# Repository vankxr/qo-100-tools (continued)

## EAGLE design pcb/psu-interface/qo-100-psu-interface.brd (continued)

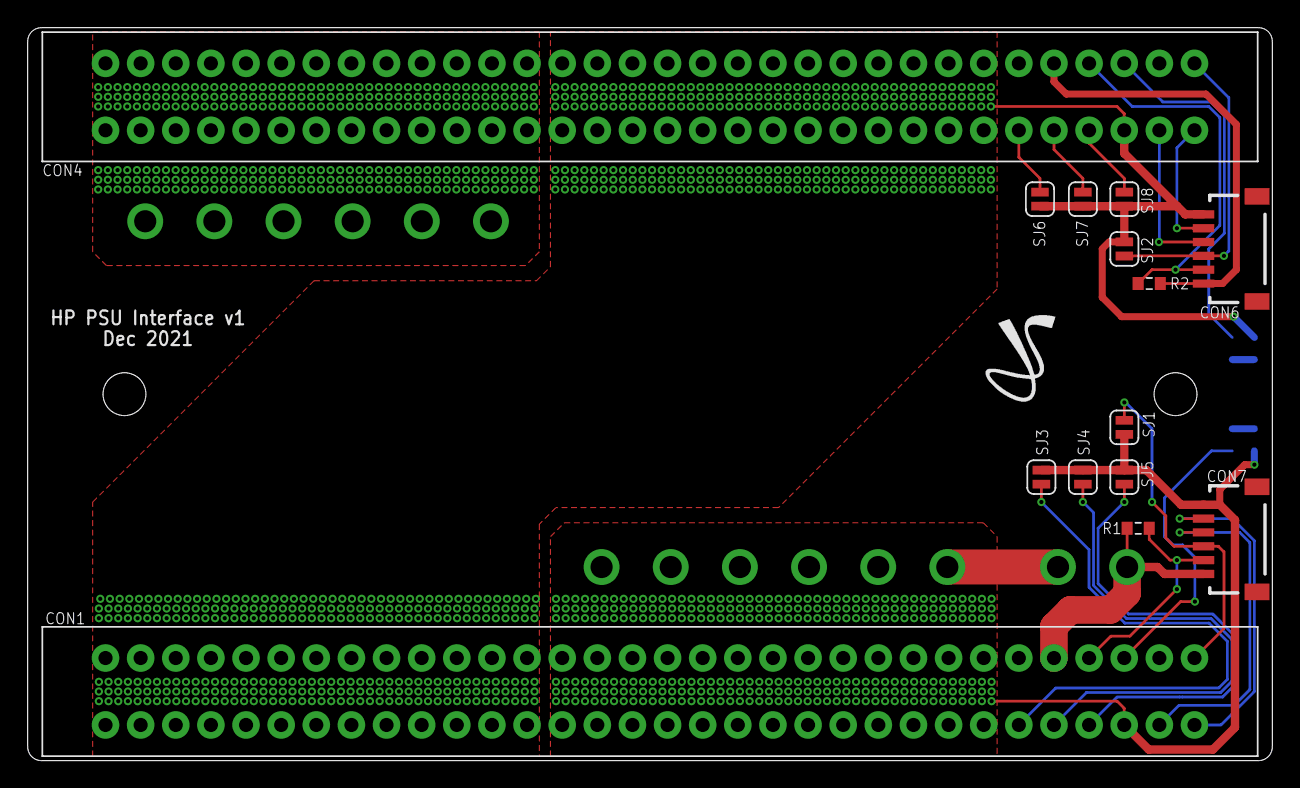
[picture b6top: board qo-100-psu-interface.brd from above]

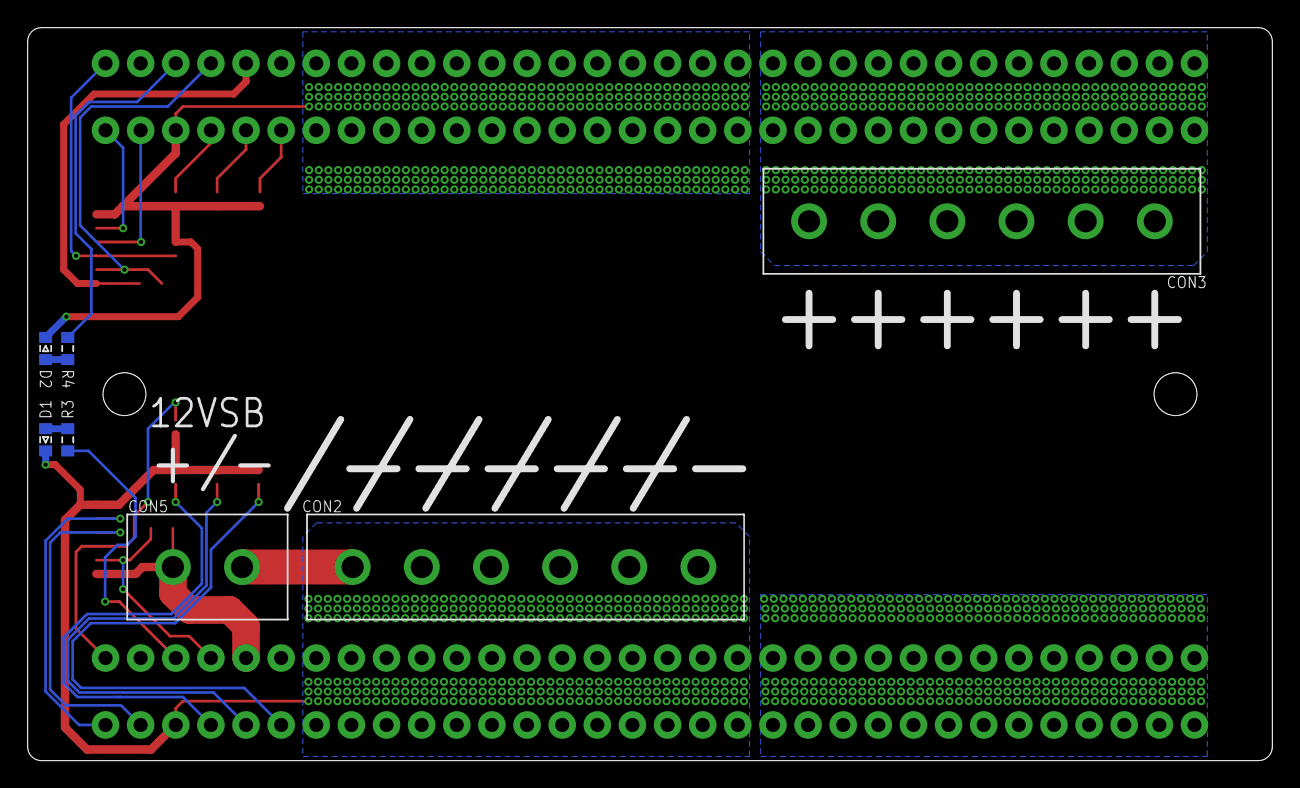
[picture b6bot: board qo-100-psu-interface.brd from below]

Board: 2 copper layers, 90.0 x 53.0 mm, 22 parts (7 on the bottom side), 23 nets.

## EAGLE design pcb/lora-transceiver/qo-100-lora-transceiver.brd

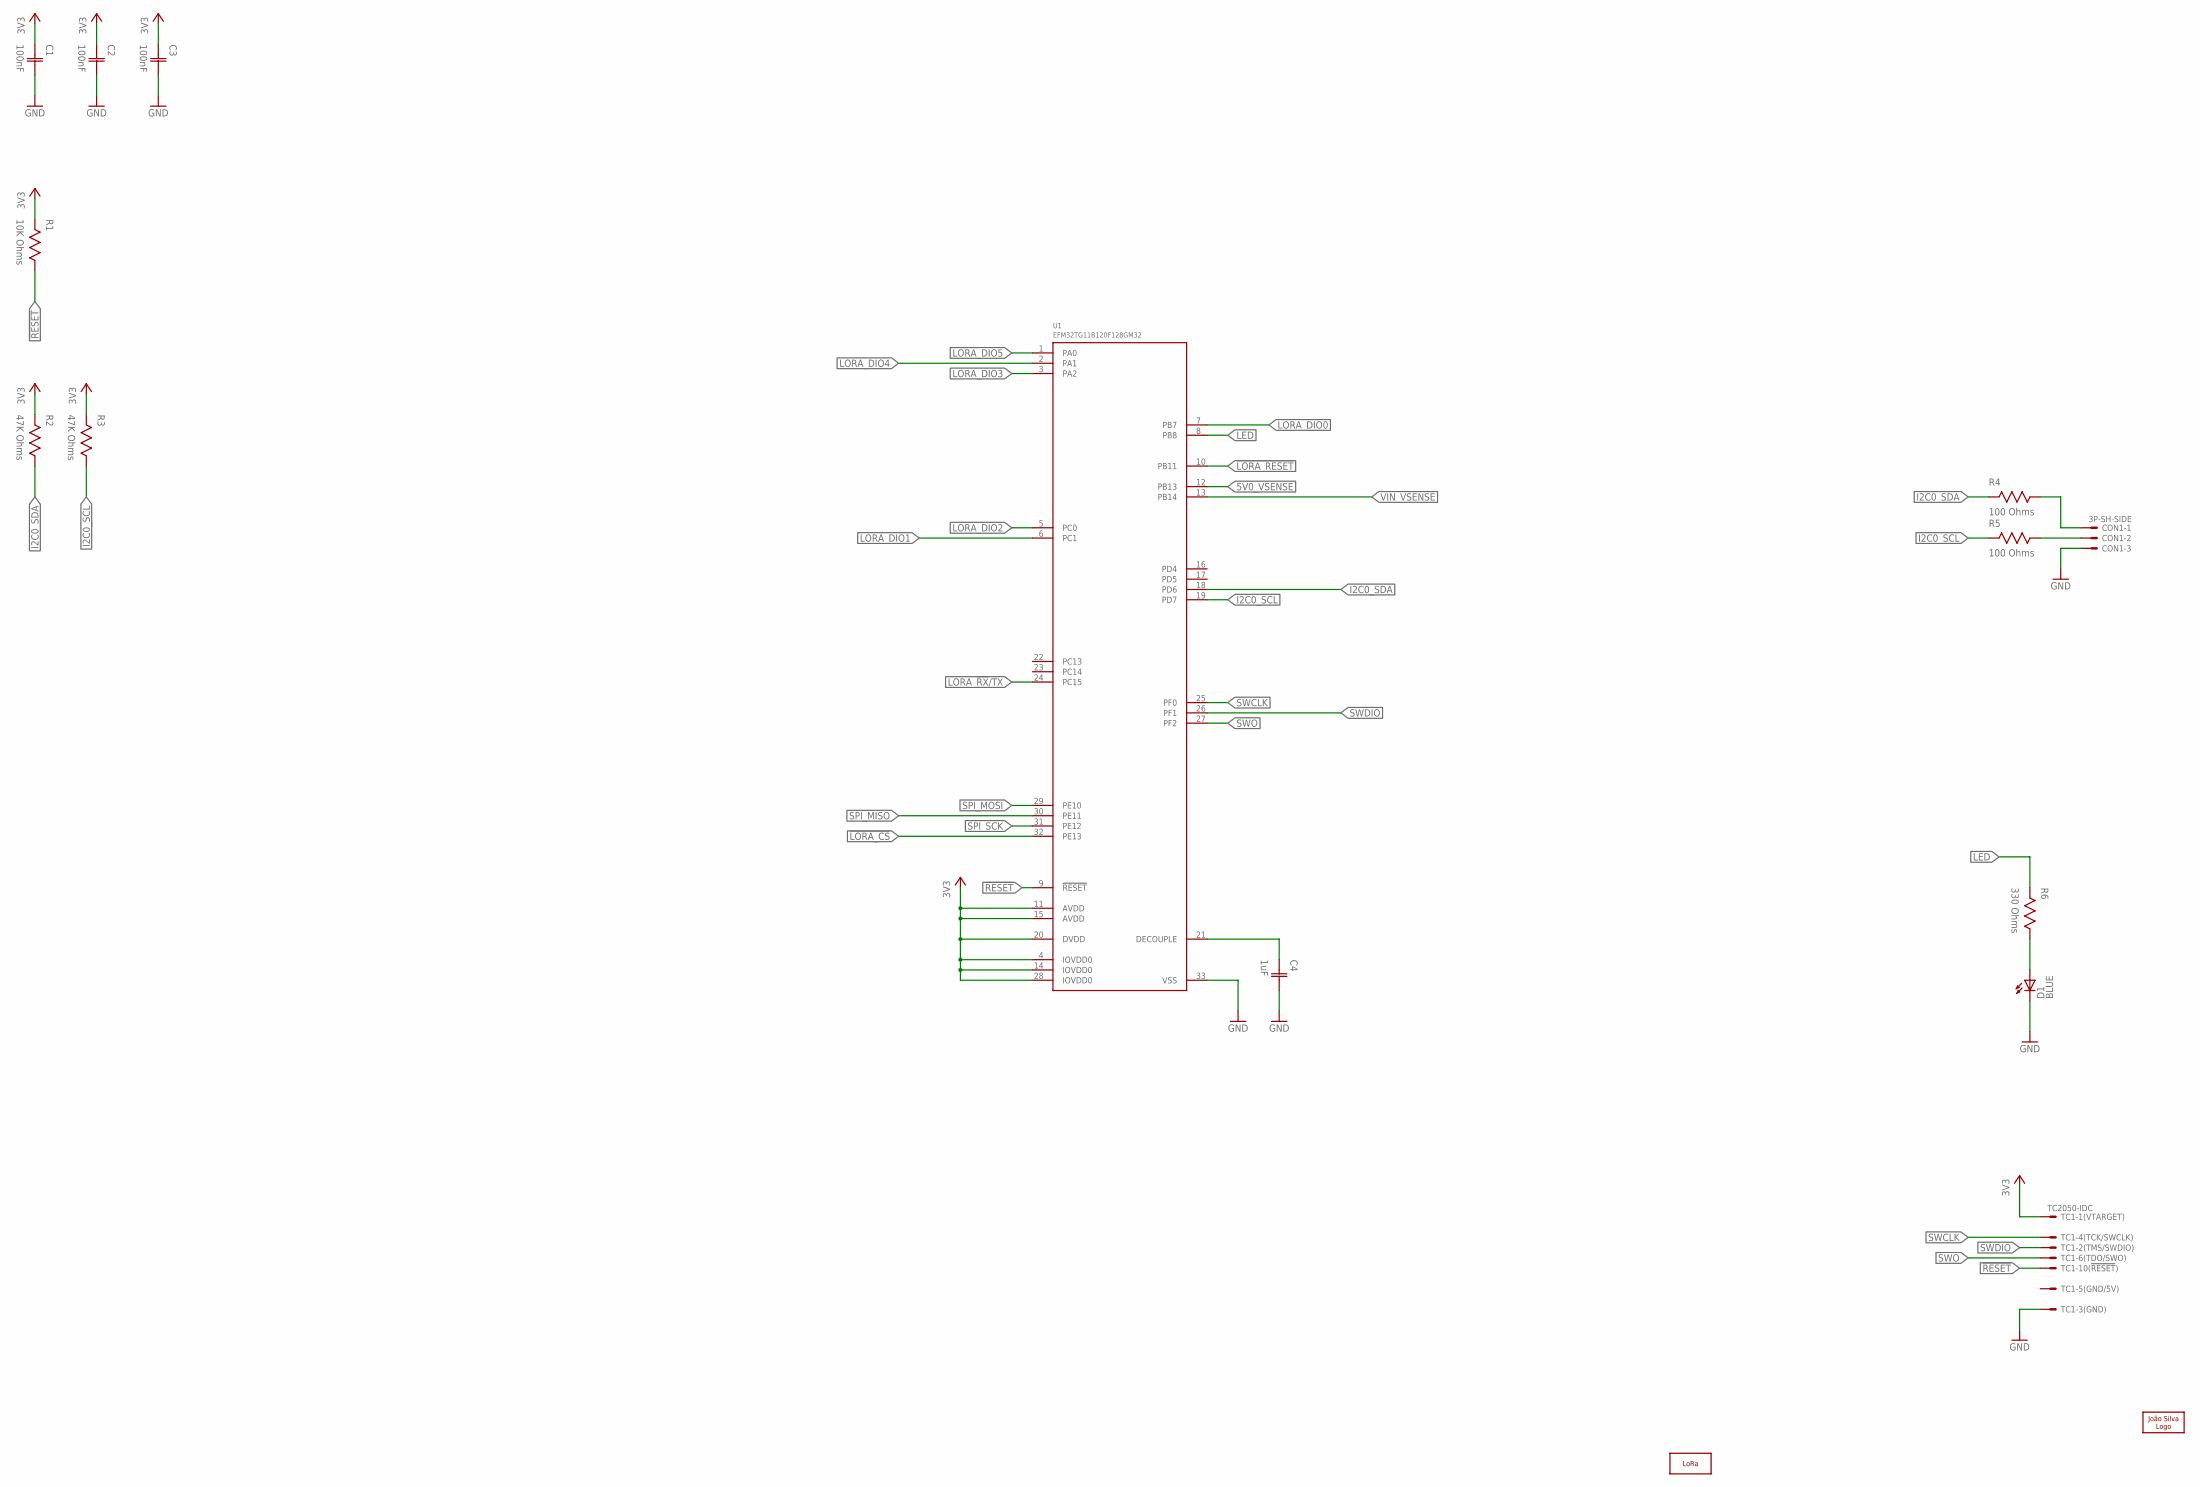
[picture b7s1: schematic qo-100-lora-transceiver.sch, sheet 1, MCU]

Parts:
C1, C2, C3: 100nF; CAP0603
C4: 1uF; CAP0603
CON1: 3P-SH-SIDE; SH-03-SIDE
D1: LED0603; 0603
LOGO1: LORA-10MM; LORA_10MM
LOGO2: JS-10MM; JS_10MM
R1: 10K Ohms; RES0603
R2, R3: 47K Ohms; RES0603
R4, R5: 100 Ohms; RES0603
R6: 330 Ohms; RES0603
TC1: TC2050-IDC
U1: EFM32TG11B120F128GM32; QFN32_0.5P_TG

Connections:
3V3: C1.1 (C1), C2.1 (C1), C3.1 (C1), R1.2, R2.2, R3.2, TC1.1, U1.4 (IOVDD0), U1.11 (AVDD), U1.14 (IOVDD0), U1.15 (AVDD), U1.20 (DVDD), U1.28 (IOVDD0); also elsewhere on the board
5V0_VSENSE: U1.12 (PB13); also elsewhere on the board
!LORA_CS: U1.32 (PE13); also elsewhere on the board
!LORA_RESET: U1.10 (PB11); also elsewhere on the board
!RESET: R1.1, TC1.10, U1.9 (!RESET)
GND: C1.2 (C2), C2.2 (C2), C3.2 (C2), C4.2 (C2), CON1.3, D1.C, TC1.3, U1.33 (VSS); also elsewhere on the board
I2C0_SCL: R3.1, R5.2, U1.19 (PD7)
I2C0_SDA: R2.1, R4.2, U1.18 (PD6)
LED: R6.2, U1.8 (PB8)
LORA_!RX!/TX: U1.24 (PC15); also elsewhere on the board
LORA_DIO0: U1.7 (PB7); also elsewhere on the board
LORA_DIO1: U1.6 (PC1); also elsewhere on the board
LORA_DIO2: U1.5 (PC0); also elsewhere on the board
LORA_DIO3: U1.3 (PA2); also elsewhere on the board
LORA_DIO4: U1.2 (PA1); also elsewhere on the board
LORA_DIO5: U1.1 (PA0); also elsewhere on the board
unnamed: CON1.2, R5.1
unnamed: C4.1 (C1), U1.21 (DECOUPLE)
unnamed: D1.A, R6.1
unnamed: CON1.1, R4.1
SPI_MISO: U1.30 (PE11); also elsewhere on the board
SPI_MOSI: U1.29 (PE10); also elsewhere on the board
SPI_SCK: U1.31 (PE12); also elsewhere on the board
SWCLK: TC1.4, U1.25 (PF0)
SWDIO: TC1.2, U1.26 (PF1)
SWO: TC1.6, U1.27 (PF2)
VIN_VSENSE: U1.13 (PB14); also elsewhere on the board

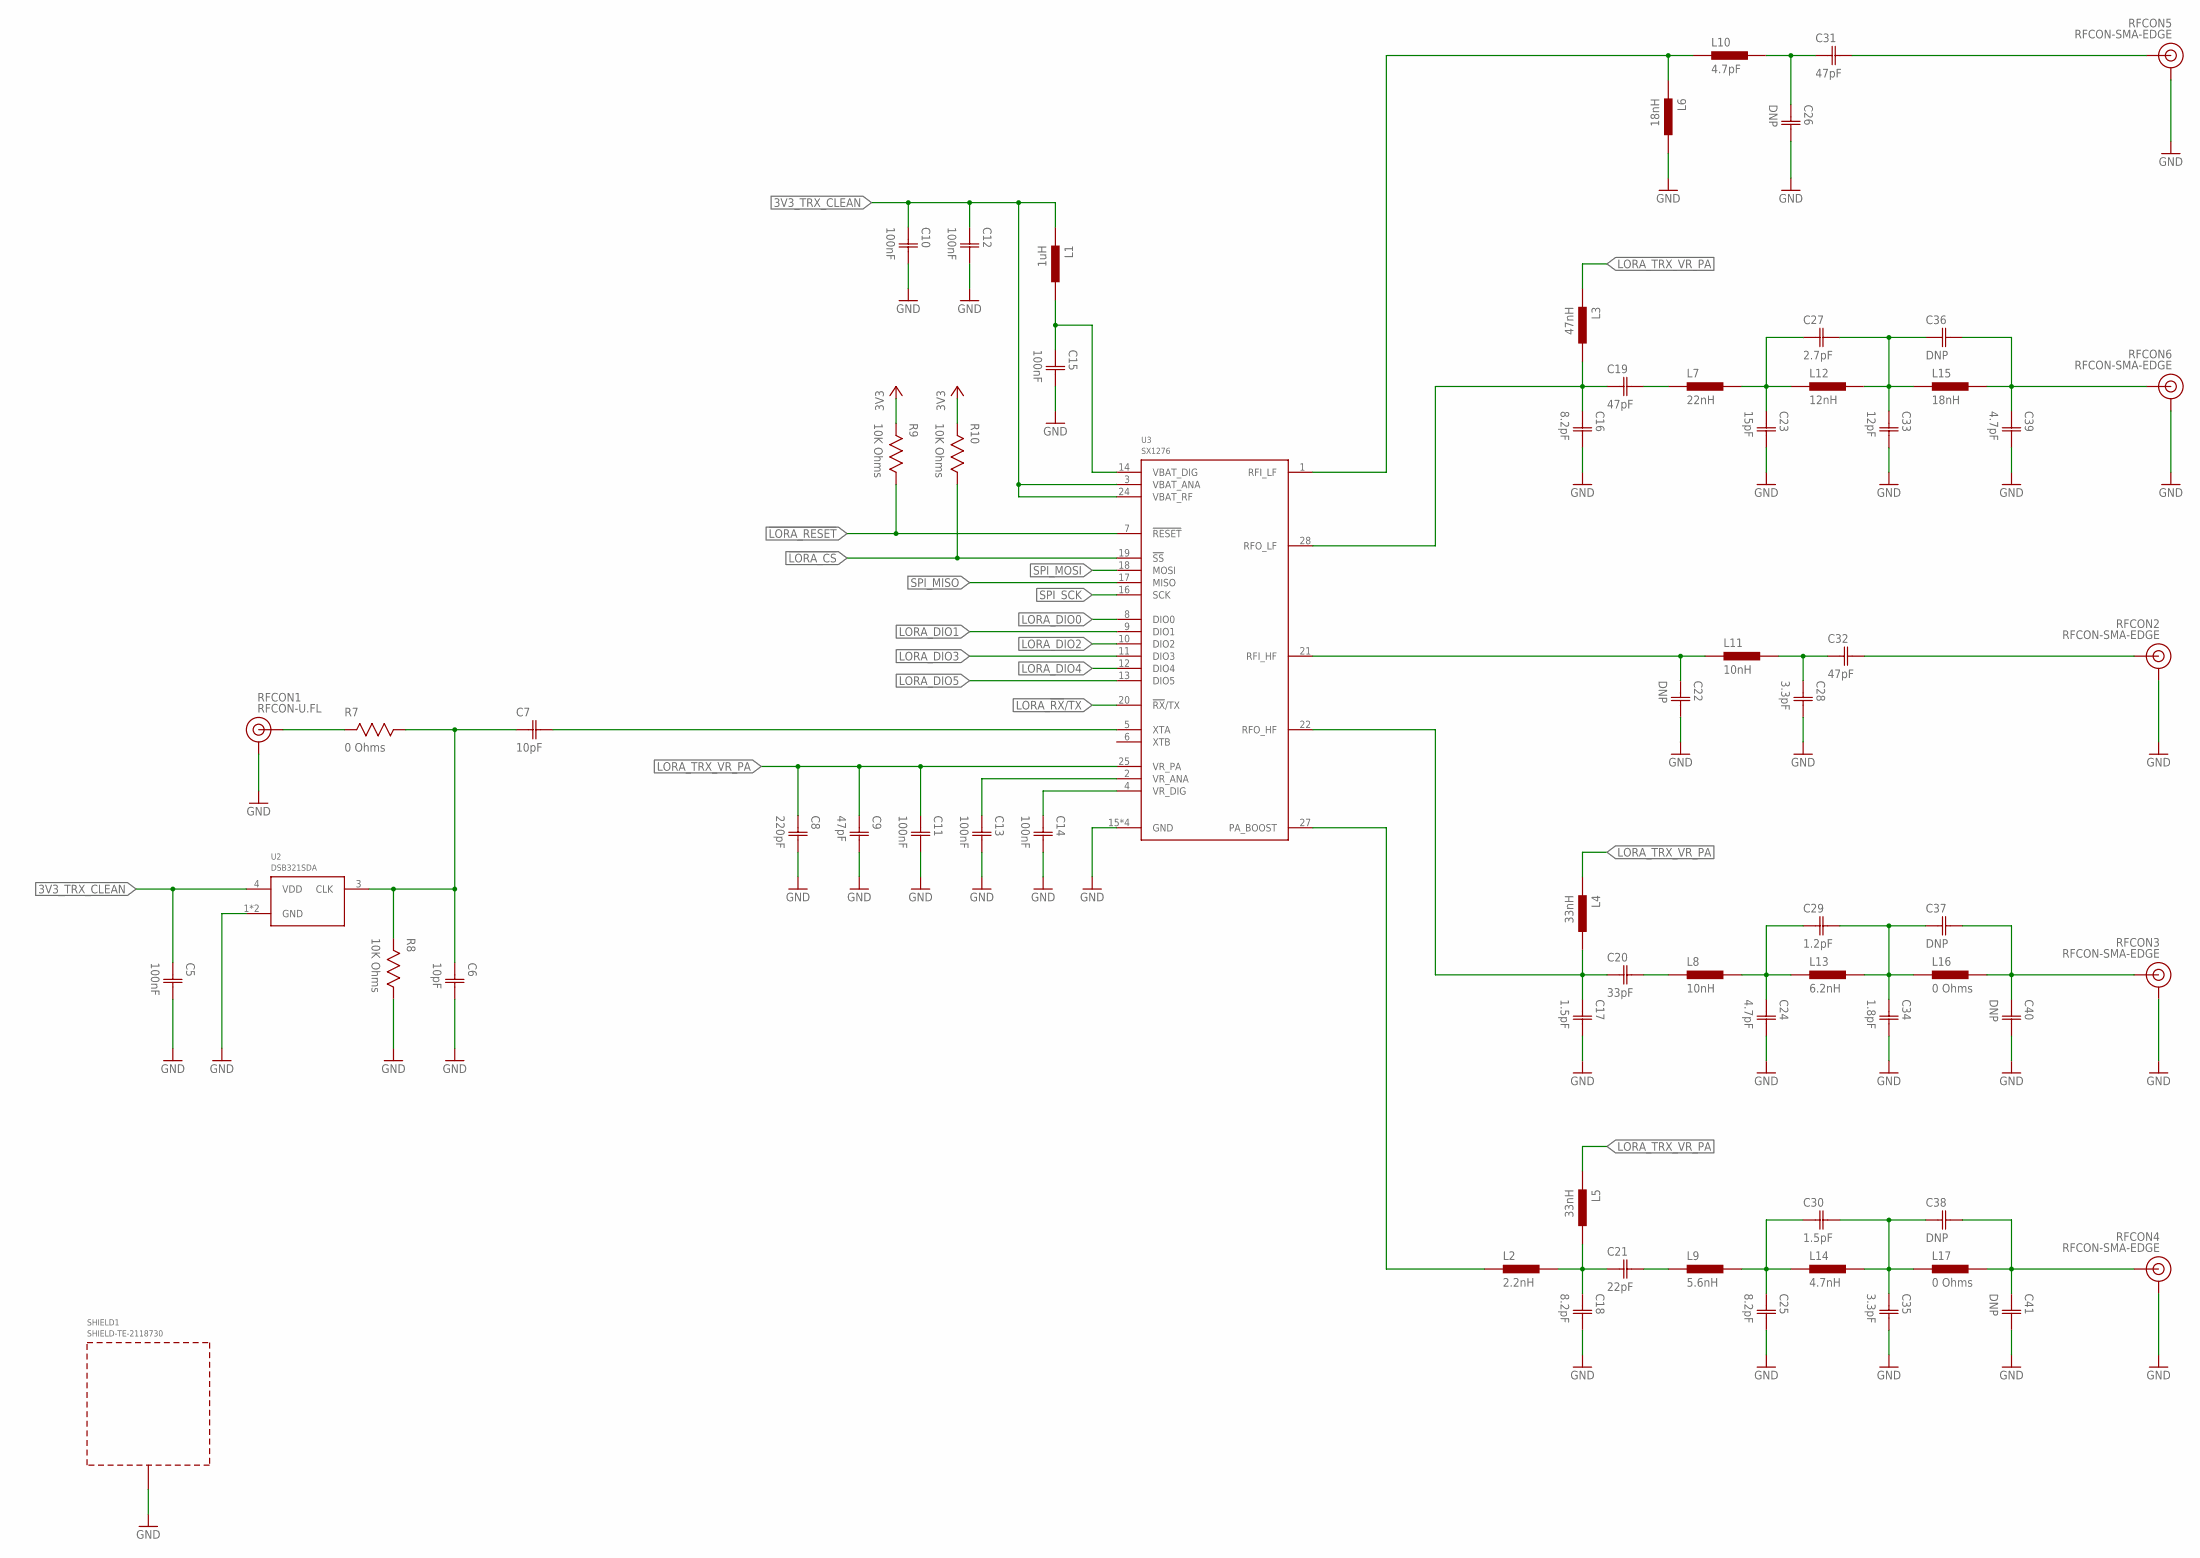
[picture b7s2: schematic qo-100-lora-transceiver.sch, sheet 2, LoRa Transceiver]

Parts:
C5, C10, C11, C12, C13, C14, C15: 100nF; CAP0603
C6, C7: 10pF; CAP0603
C8: 220pF; CAP0603
C9, C19, C31, C32: 47pF; CAP0603
C16, C18, C25: 8.2pF; CAP0603
C17, C30: 1.5pF; CAP0603
C20: 33pF; CAP0603
C21: 22pF; CAP0603
C22, C26, C36, C37, C38, C40, C41: DNP; CAP0603
C23: 15pF; CAP0603
C24, C39: 4.7pF; CAP0603
C27: 2.7pF; CAP0603
C28, C35: 3.3pF; CAP0603
C29: 1.2pF; CAP0603
C33: 12pF; CAP0603
C34: 1.8pF; CAP0603
L1: 1uH; IND0603
L2: 2.2nH; IND0603
L3: 47nH; IND0603
L4, L5: 33nH; IND0603
L6, L15: 18nH; IND0603
L7: 22nH; IND0603
L8, L11: 10nH; IND0603
L9: 5.6nH; IND0603
L10: 4.7pF; IND0603
L12: 12nH; IND0603
L13: 6.2nH; IND0603
L14: 4.7nH; IND0603
L16, L17: 0 Ohms; IND0603
R7: 0 Ohms; RES0603
R8, R9, R10: 10K Ohms; RES0603
RFCON1: RFCON-U.FL; U.FL
RFCON2, RFCON3, RFCON4, RFCON5, RFCON6: RFCON-SMA-EDGE; SMA-EDGE
SHIELD1: SHIELD-TE-2118730; 2118730
U2: DSB321SDA; TCXO-3225
U3: SX1276; QFN28

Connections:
3V3: R9.2, R10.2; also elsewhere on the board
3V3_TRX_CLEAN: C5.1 (C1), C10.1 (C1), C12.1 (C1), L1.1, U2.4 (VDD), U3.3 (VBAT_ANA), U3.24 (VBAT_RF); also elsewhere on the board
!LORA_CS: R10.1, U3.19 (!SS); also elsewhere on the board
!LORA_RESET: R9.1, U3.7 (!RESET); also elsewhere on the board
GND: C5.2 (C2), C6.2 (C2), C8.2 (C2), C9.2 (C2), C10.2 (C2), C11.2 (C2), C12.2 (C2), C13.2 (C2), C14.2 (C2), C15.2 (C2), C16.2 (C2), C17.2 (C2), C18.2 (C2), C22.2 (C2), C23.2 (C2), C24.2 (C2), C25.2 (C2), C26.2 (C2), C28.2 (C2), C33.2 (C2), C34.2 (C2), C35.2 (C2), C39.2 (C2), C40.2 (C2), C41.2 (C2), L6.2, R8.1, RFCON1.P$1 (GND), RFCON1.P$2 (GND), RFCON2.GND@0 (GND), RFCON2.GND@1 (GND), RFCON2.GND@2 (GND), RFCON2.GND@3 (GND), RFCON3.GND@0 (GND), RFCON3.GND@1 (GND), RFCON3.GND@2 (GND), RFCON3.GND@3 (GND), RFCON4.GND@0 (GND), RFCON4.GND@1 (GND), RFCON4.GND@2 (GND), RFCON4.GND@3 (GND), RFCON5.GND@0 (GND), RFCON5.GND@1 (GND), RFCON5.GND@2 (GND), RFCON5.GND@3 (GND), RFCON6.GND@0 (GND), RFCON6.GND@1 (GND), RFCON6.GND@2 (GND), RFCON6.GND@3 (GND), SHIELD1.1, SHIELD1.2, SHIELD1.3, SHIELD1.4, SHIELD1.5, SHIELD1.6, SHIELD1.7, SHIELD1.8, SHIELD1.9, SHIELD1.10, SHIELD1.11, SHIELD1.12, SHIELD1.13, SHIELD1.14, SHIELD1.15, SHIELD1.16, SHIELD1.17, SHIELD1.18, SHIELD1.19, SHIELD1.20, SHIELD1.21, SHIELD1.22, SHIELD1.23, SHIELD1.24, SHIELD1.25, SHIELD1.26, SHIELD1.27, SHIELD1.28, U2.1 (GND), U2.2 (GND), U3.15 (GND), U3.23 (GND), U3.26 (GND), U3.29 (GND); also elsewhere on the board
LORA_!RX!/TX: U3.20 (!RX!/TX); also elsewhere on the board
LORA_DIO0: U3.8 (DIO0); also elsewhere on the board
LORA_DIO1: U3.9 (DIO1); also elsewhere on the board
LORA_DIO2: U3.10 (DIO2); also elsewhere on the board
LORA_DIO3: U3.11 (DIO3); also elsewhere on the board
LORA_DIO4: U3.12 (DIO4); also elsewhere on the board
LORA_DIO5: U3.13 (DIO5); also elsewhere on the board
LORA_TRX_VR_ANA: C13.1 (C1), U3.2 (VR_ANA)
LORA_TRX_VR_DIG: C14.1 (C1), U3.4 (VR_DIG)
LORA_TRX_VR_PA: C8.1 (C1), C9.1 (C1), C11.1 (C1), L3.1, L4.1, L5.1, U3.25 (VR_PA)
unnamed: C15.1 (C1), L1.2, U3.14 (VBAT_DIG)
unnamed: C16.1 (C1), C19.1 (C1), L3.2, U3.28 (RFO_LF)
unnamed: C19.2 (C2), L7.1
unnamed: C23.1 (C1), C27.1 (C1), L7.2, L12.1
unnamed: C27.2 (C2), C33.1 (C1), C36.1 (C1), L12.2, L15.1
unnamed: C22.1 (C1), L11.1, U3.21 (RFI_HF)
unnamed: L6.1, L10.1, U3.1 (RFI_LF)
unnamed: C26.1 (C1), C31.1 (C1), L10.2
unnamed: C17.1 (C1), C20.1 (C1), L4.2, U3.22 (RFO_HF)
unnamed: C20.2 (C2), L8.1
unnamed: C24.1 (C1), C29.1 (C1), L8.2, L13.1
unnamed: C29.2 (C2), C34.1 (C1), C37.1 (C1), L13.2, L16.1
unnamed: C37.2 (C2), C40.1 (C1), L16.2, RFCON3.SIG (SIGNAL)
unnamed: C28.1 (C1), C32.1 (C1), L11.2
unnamed: L2.1, U3.27 (PA_BOOST)
unnamed: C18.1 (C1), C21.1 (C1), L2.2, L5.2
unnamed: C36.2 (C2), C39.1 (C1), L15.2, RFCON6.SIG (SIGNAL)
unnamed: C21.2 (C2), L9.1
unnamed: C25.1 (C1), C30.1 (C1), L9.2, L14.1
unnamed: C30.2 (C2), C35.1 (C1), C38.1 (C1), L14.2, L17.1
unnamed: C38.2 (C2), C41.1 (C1), L17.2, RFCON4.SIG (SIGNAL)
unnamed: C31.2 (C2), RFCON5.SIG (SIGNAL)
unnamed: C32.2 (C2), RFCON2.SIG (SIGNAL)
unnamed: C7.2 (C2), U3.5 (XTA)
unnamed: R7.2, RFCON1.P$3 (SIGNAL)
PLL_REF_DCC: C6.1 (C1), C7.1 (C1), R7.1, R8.2, U2.3 (CLK)
SPI_MISO: U3.17 (MISO); also elsewhere on the board
SPI_MOSI: U3.18 (MOSI); also elsewhere on the board
SPI_SCK: U3.16 (SCK); also elsewhere on the board

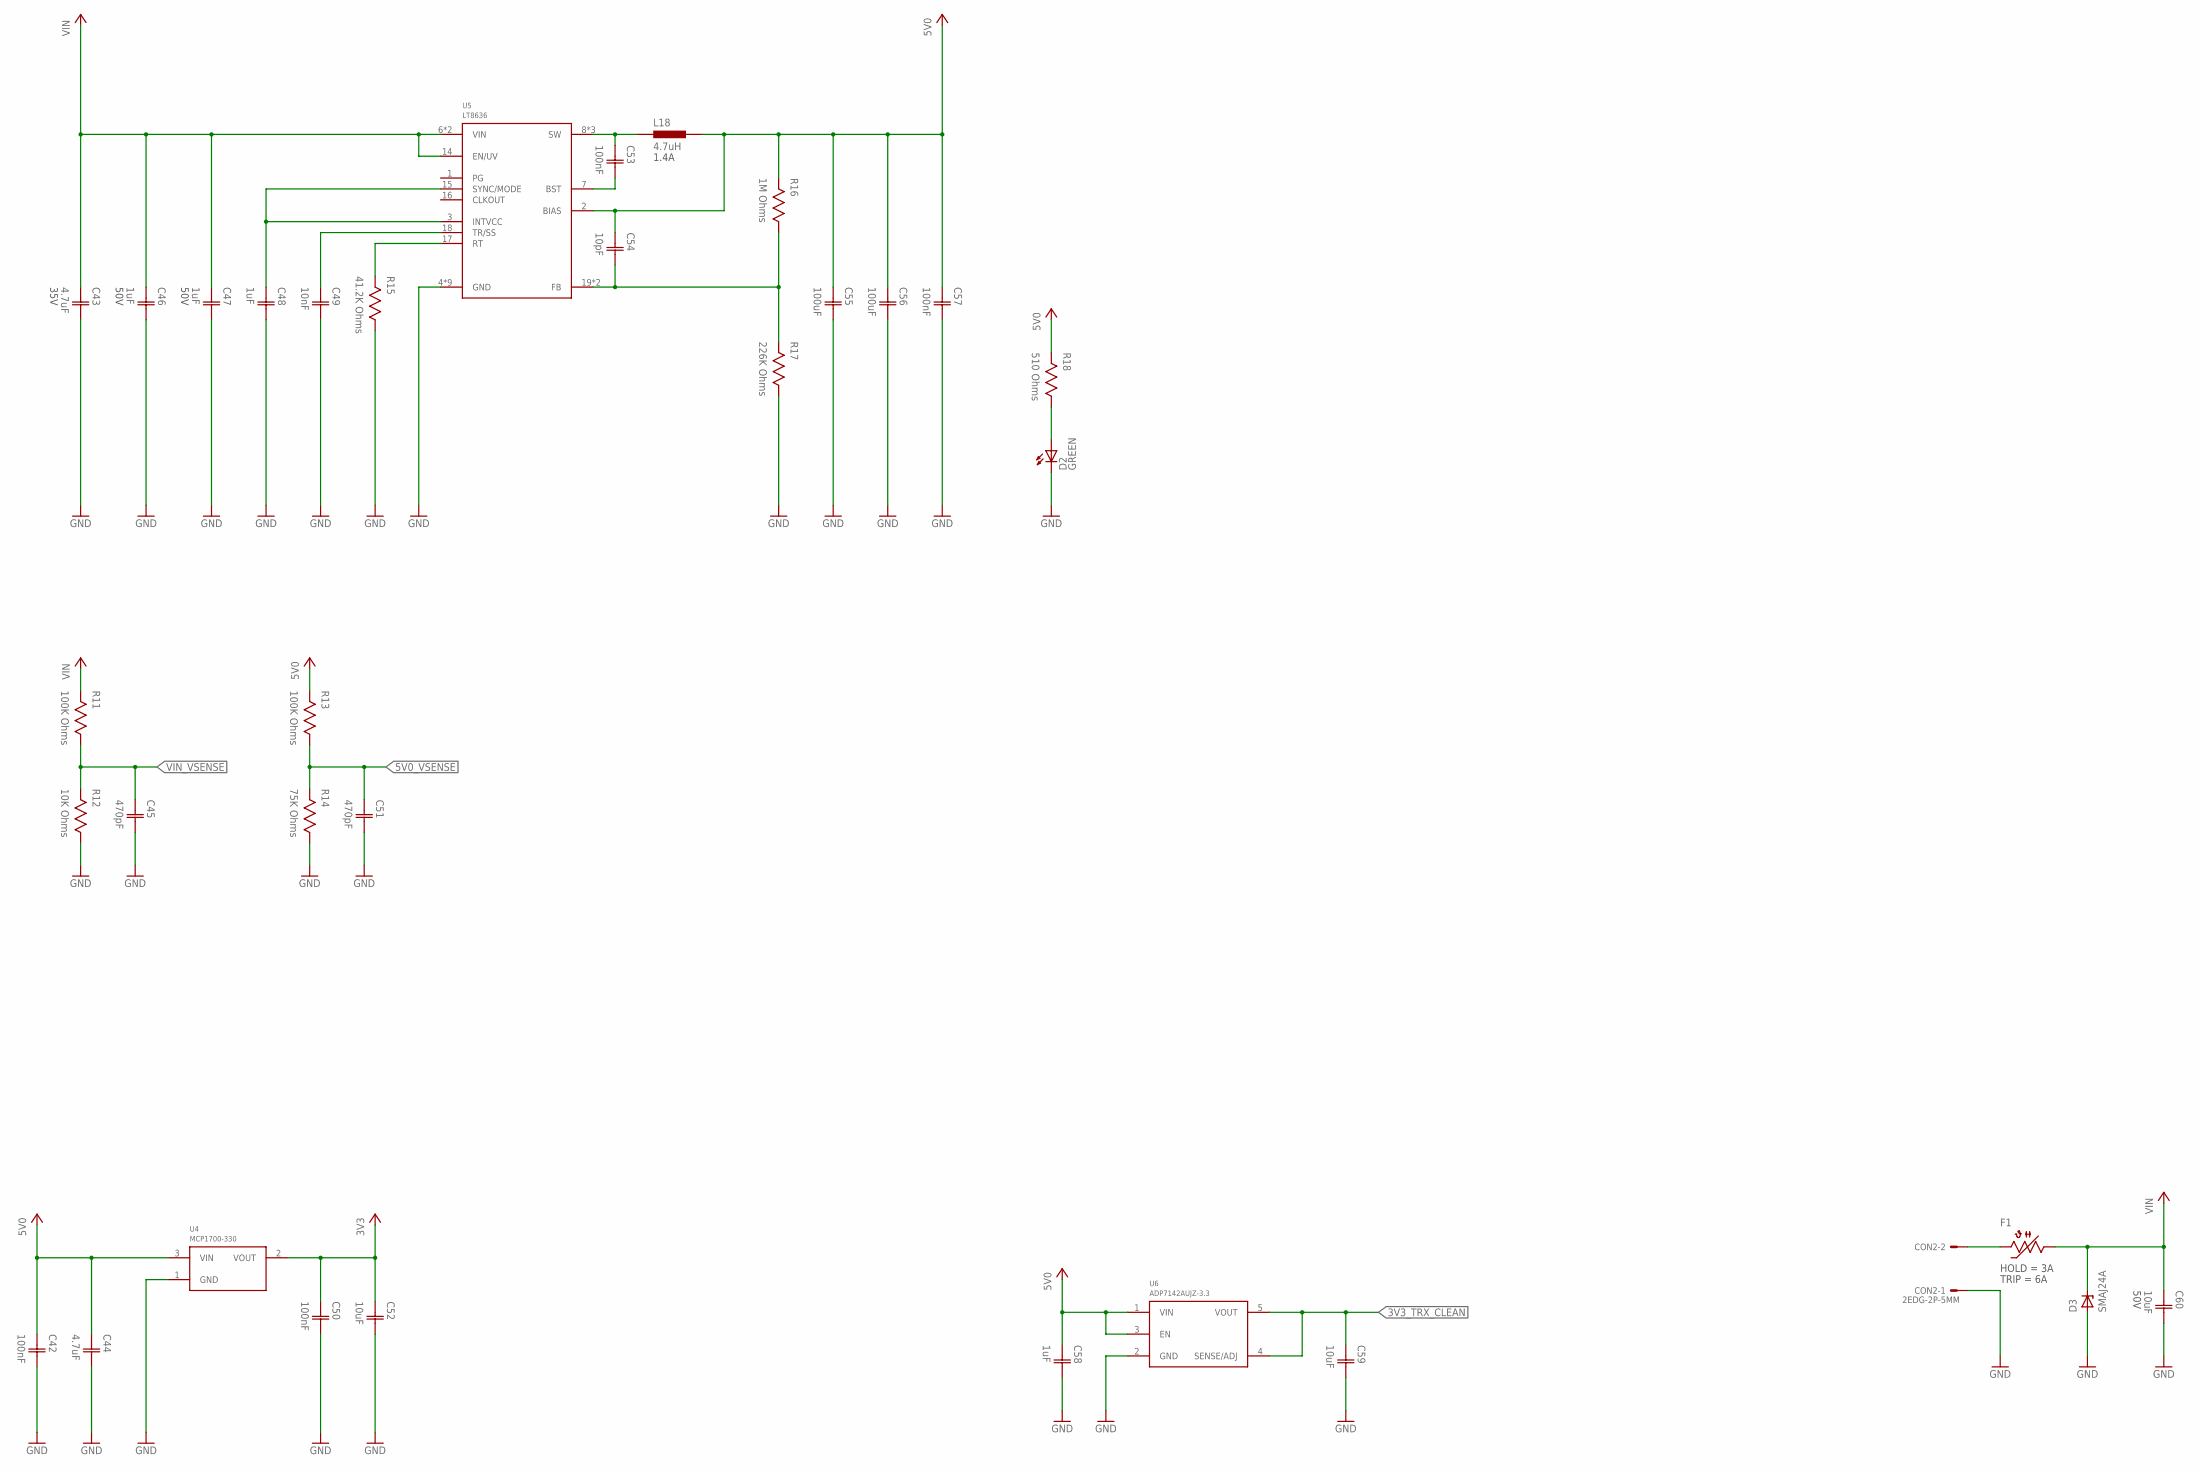
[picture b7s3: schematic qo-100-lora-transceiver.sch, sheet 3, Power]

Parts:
C42, C50, C53, C57: 100nF; CAP0603
C43: 4.7uF; CAP0603; VOLTAGE 35V
C44: 4.7uF; CAP0603
C45, C51: 470pF; CAP0603
C46, C47: 1uF; CAP0603; VOLTAGE 50V
C48, C58: 1uF; CAP0603
C49: 10nF; CAP0603
C52, C59: 10uF; CAP0603
C54: 10pF; CAP0603
C55, C56: 100uF; CAP1206
C60: 10uF; CAP1206; VOLTAGE 50V
CON2: 2EDG-2P-5MM
D2: LED0603; 0603
D3: SMAJ24A; DO214AC
F1: 2.6A Hold; 1206
L18: 4.7uH; IND2520
R11, R13: 100K Ohms; RES0603
R12: 10K Ohms; RES0603
R14: 75K Ohms; RES0603
R15: 41.2K Ohms; RES0603
R16: 1M Ohms; RES0603
R17: 226K Ohms; RES0603
R18: 510 Ohms; RES0603
U4: MCP1700-330; SOT23
U5: LT8636; QFN20_ASYM_CORNER
U6: ADP7142AUJZ-3.3; SOT23-5

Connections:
3V3: C50.1 (C1), C52.1 (C1), U4.2 (VOUT); also elsewhere on the board
3V3_TRX_CLEAN: C59.1 (C1), U6.4 (SENSE/ADJ), U6.5 (VOUT); also elsewhere on the board
5V0: C42.1 (C1), C44.1 (C1), C54.1 (C1), C55.1 (C1), C56.1 (C1), C57.1 (C1), C58.1 (C1), L18.2, R13.2, R16.2, R18.2, U4.3 (VIN), U5.2 (BIAS), U6.1 (VIN), U6.3 (EN)
5V0_BST: C53.2 (C2), U5.7 (BST)
5V0_FB: C54.2 (C2), R16.1, R17.2, U5.19 (FB), U5.20 (FB)
5V0_INTVCC: C48.1 (C1), U5.3 (INTVCC), U5.15 (SYNC/MODE)
5V0_RT: R15.2, U5.17 (RT)
5V0_SS: C49.1 (C1), U5.18 (TR/SS)
5V0_SW: C53.1 (C1), L18.1, U5.8 (SW), U5.9 (SW), U5.10 (SW)
5V0_VSENSE: C51.1 (C1), R13.1, R14.2; also elsewhere on the board
GND: C42.2 (C2), C43.2 (C2), C44.2 (C2), C45.2 (C2), C46.2 (C2), C47.2 (C2), C48.2 (C2), C49.2 (C2), C50.2 (C2), C51.2 (C2), C52.2 (C2), C55.2 (C2), C56.2 (C2), C57.2 (C2), C58.2 (C2), C59.2 (C2), C60.2 (C2), CON2.P$1, D2.C, D3.A, R12.1, R14.1, R15.1, R17.1, U4.1 (GND), U5.4 (GND), U5.5 (GND), U5.12 (GND), U5.13 (GND), U5.21 (GND), U5.M1 (GND), U5.M2 (GND), U5.M3 (GND), U5.M4 (GND), U6.2 (GND); also elsewhere on the board
unnamed: CON2.P$2, F1.2
unnamed: D2.A, R18.1
VIN: C43.1 (C1), C46.1 (C1), C47.1 (C1), C60.1 (C1), D3.C, F1.1, R11.2, U5.6 (VIN), U5.11 (VIN), U5.14 (EN/UV)
VIN_VSENSE: C45.1 (C1), R11.1, R12.2; also elsewhere on the board

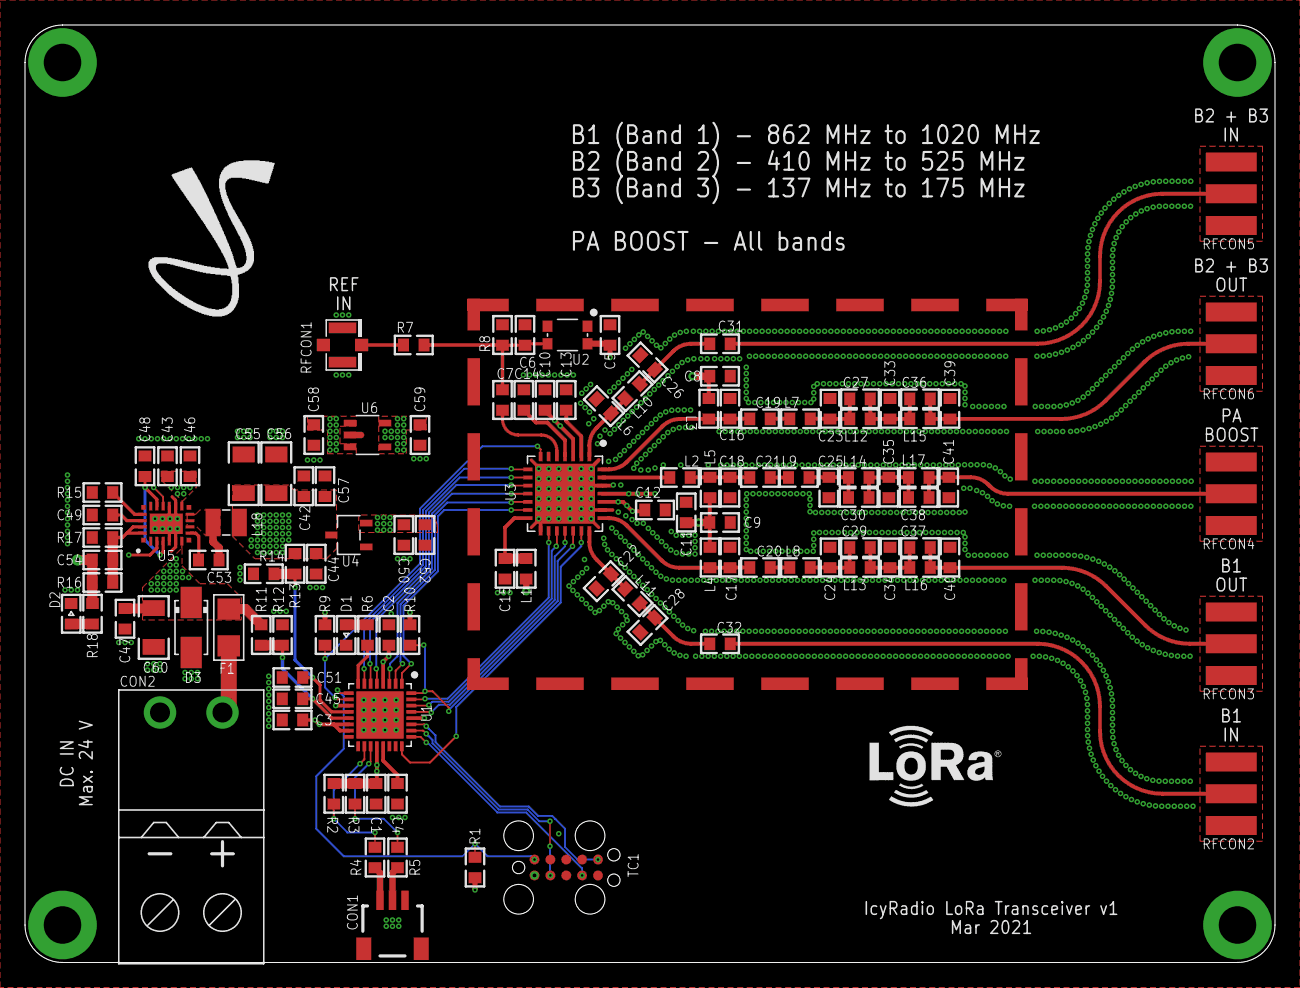
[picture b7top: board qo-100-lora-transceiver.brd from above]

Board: 4 copper layers, 100.0 x 75.0 mm, 118 parts (0 on the bottom side), 67 nets.

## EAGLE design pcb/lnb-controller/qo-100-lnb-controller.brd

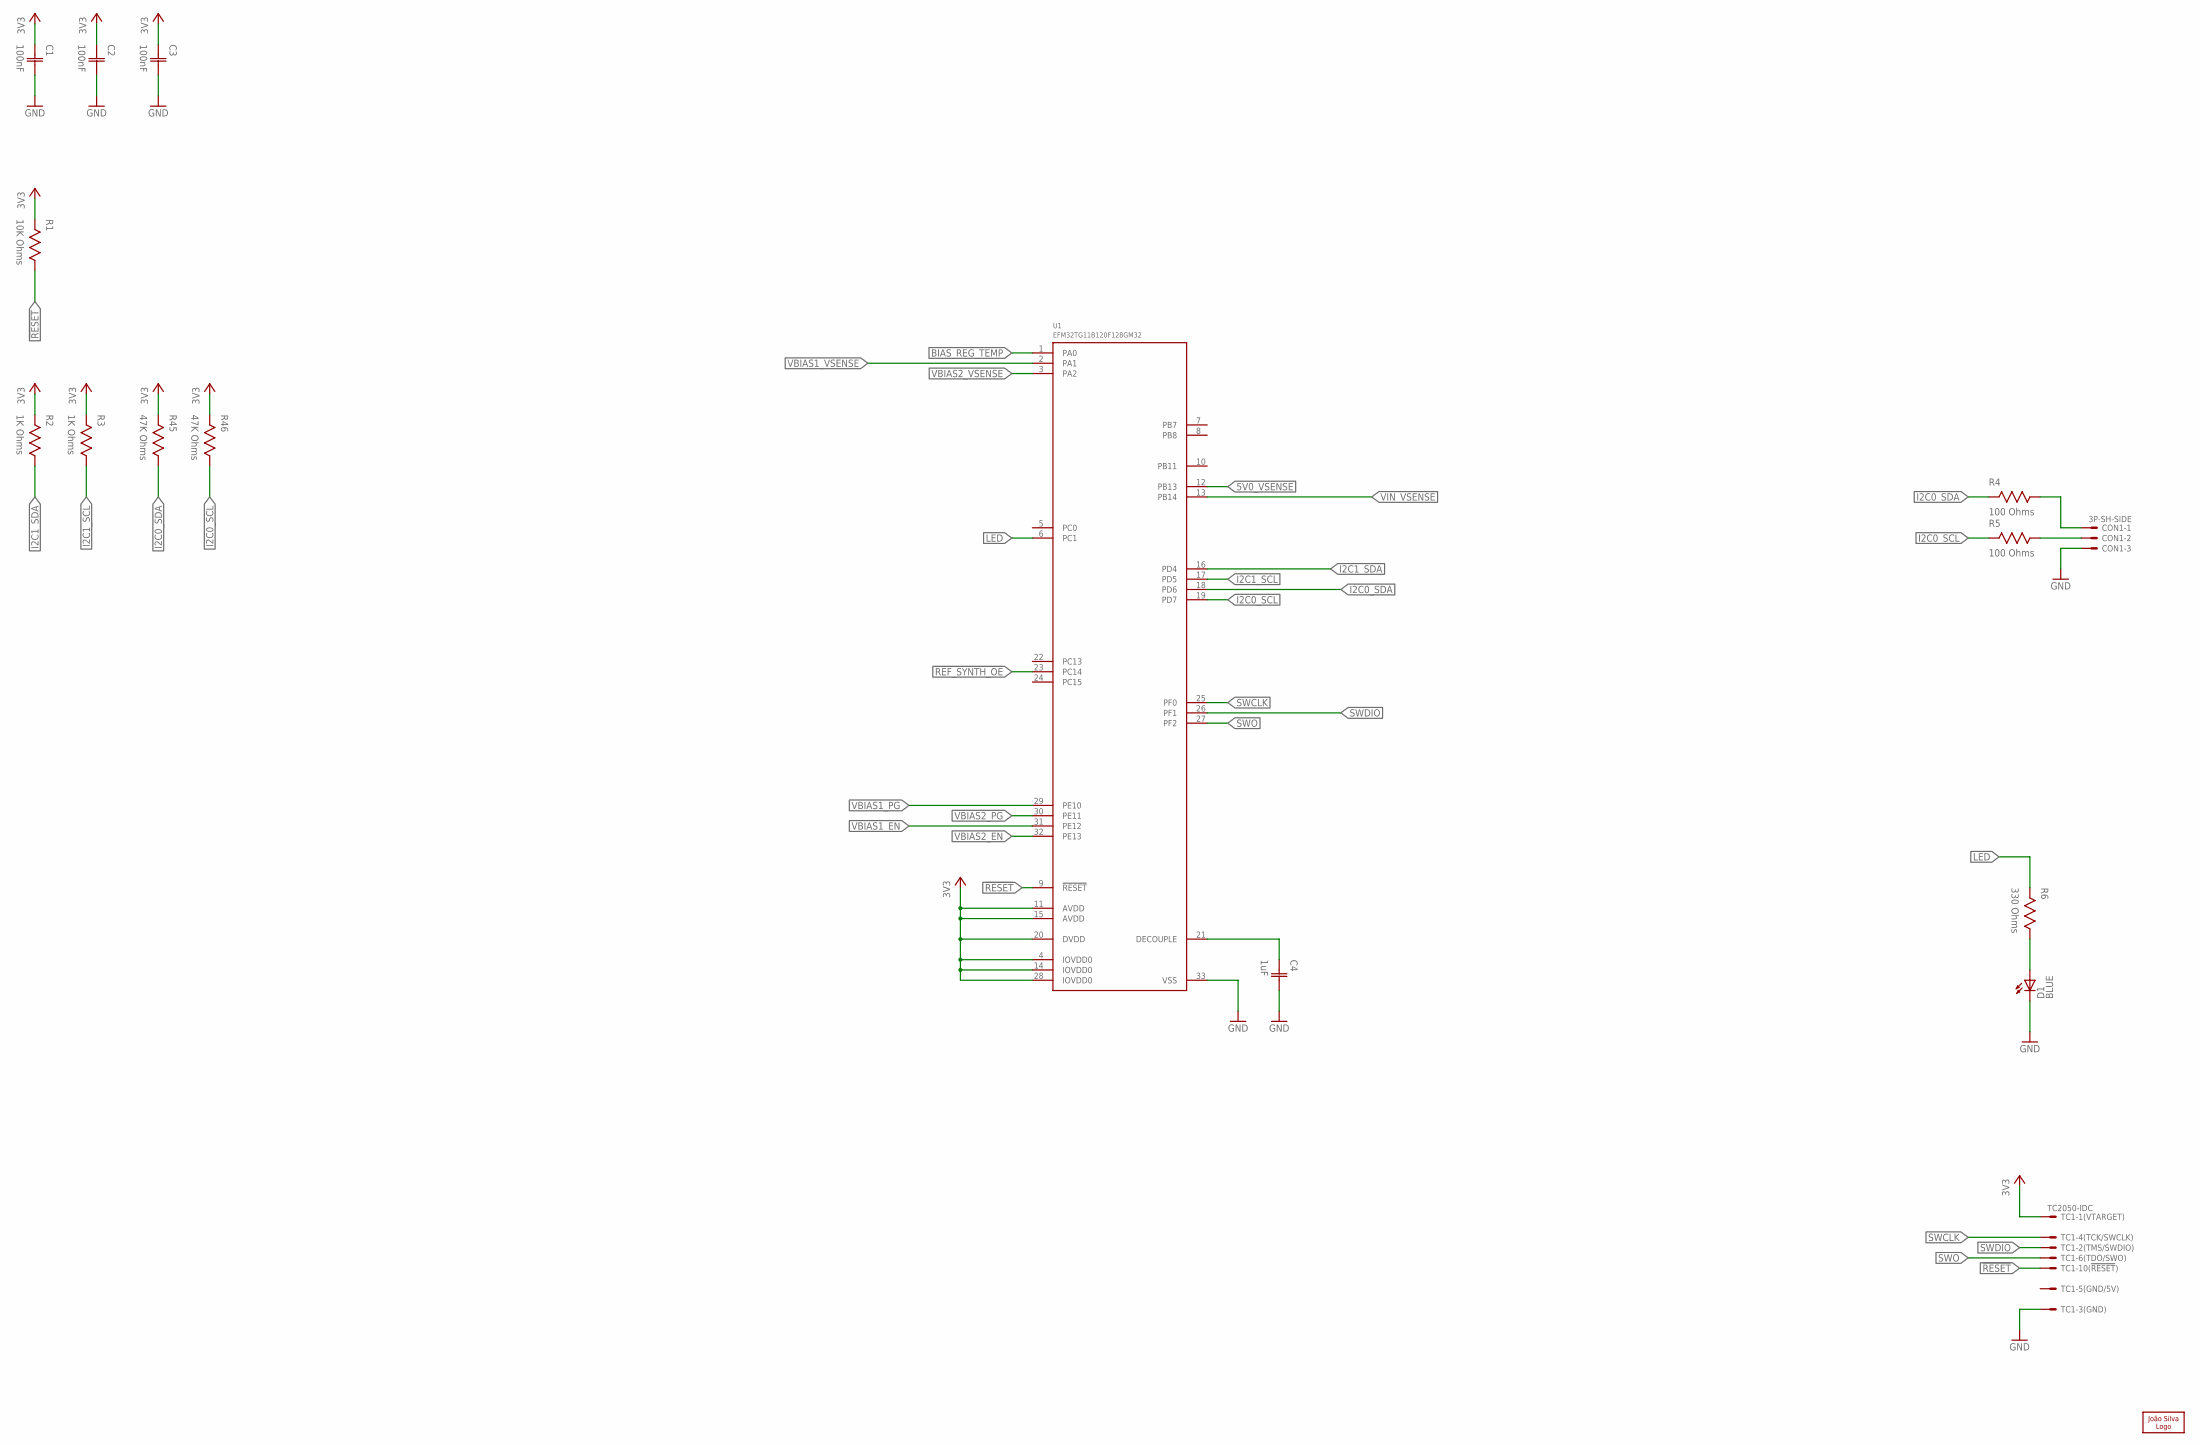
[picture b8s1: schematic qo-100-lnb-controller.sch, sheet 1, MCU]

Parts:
C1, C2, C3: 100nF; CAP0603
C4: 1uF; CAP0603
CON1: 3P-SH-SIDE; SH-03-SIDE
D1: LED0603; 0603
LOGO1: JS-10MM; JS_10MM
R1: 10K Ohms; RES0603
R2, R3: 1K Ohms; RES0603
R4, R5: 100 Ohms; RES0603
R6: 330 Ohms; RES0603
R45, R46: 47K Ohms; RES0603
TC1: TC2050-IDC
U1: EFM32TG11B120F128GM32; QFN32_0.5P_TG

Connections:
3V3: C1.1 (C1), C2.1 (C1), C3.1 (C1), R1.2, R2.2, R3.2, R45.2, R46.2, TC1.1, U1.4 (IOVDD0), U1.11 (AVDD), U1.14 (IOVDD0), U1.15 (AVDD), U1.20 (DVDD), U1.28 (IOVDD0); also elsewhere on the board
5V0_VSENSE: U1.12 (PB13); also elsewhere on the board
!REF_SYNTH_OE: U1.23 (PC14); also elsewhere on the board
!RESET: R1.1, TC1.10, U1.9 (!RESET)
BIAS_REG_TEMP: U1.1 (PA0); also elsewhere on the board
GND: C1.2 (C2), C2.2 (C2), C3.2 (C2), C4.2 (C2), CON1.3, D1.C, TC1.3, U1.33 (VSS); also elsewhere on the board
I2C0_SCL: R5.2, R46.1, U1.19 (PD7)
I2C0_SDA: R4.2, R45.1, U1.18 (PD6)
I2C1_SCL: R3.1, U1.17 (PD5); also elsewhere on the board
I2C1_SDA: R2.1, U1.16 (PD4); also elsewhere on the board
LED: R6.2, U1.6 (PC1)
unnamed: CON1.2, R5.1
unnamed: C4.1 (C1), U1.21 (DECOUPLE)
unnamed: D1.A, R6.1
unnamed: CON1.1, R4.1
SWCLK: TC1.4, U1.25 (PF0)
SWDIO: TC1.2, U1.26 (PF1)
SWO: TC1.6, U1.27 (PF2)
VBIAS1_EN: U1.31 (PE12); also elsewhere on the board
VBIAS1_PG: U1.29 (PE10); also elsewhere on the board
VBIAS1_VSENSE: U1.2 (PA1); also elsewhere on the board
VBIAS2_EN: U1.32 (PE13); also elsewhere on the board
VBIAS2_PG: U1.30 (PE11); also elsewhere on the board
VBIAS2_VSENSE: U1.3 (PA2); also elsewhere on the board
VIN_VSENSE: U1.13 (PB14); also elsewhere on the board
